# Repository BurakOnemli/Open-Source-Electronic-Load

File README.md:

# Open-Source-Electronic-Load

Welcome to the **Open-Source Electronic Load** project!

This repository provides the design, source code, and documentation for a customizable, open-source electronic load. The project is developed in C and aims to offer a platform for electronics enthusiasts, students, and engineers who need a programmable load for testing power supplies, batteries, or other electronic circuits.

## Features

- Fully open-source hardware and firmware
- Designed for flexibility and expandability
- Suitable for testing DC power supplies and batteries
- Customizable load profiles (constant current, constant power, etc.)

## Repository Structure

- **Firmware**: Source code for the microcontroller that controls the electronic load
- **Hardware**: Schematics, PCB layouts, and hardware documentation
- **Documentation**: User guides and developer notes

## Getting Started

1. **Clone the repository:**  
   `git clone https://github.com/BurakOnemli/Open-Source-Electronic-Load.git`
2. **Review the hardware documents** to understand the design and required components.
3. **Build the hardware** according to the provided schematics and BOM.
4. **Flash the firmware** onto the chosen microcontroller.

## Dependencies

- STM32CubeIDE toolchain for programming the microcontroller
- KiCad for PCB design 
- Standard electronics lab tools for assembly

## Contributing

Contributions are welcome! You can contribute by:
- Submitting pull requests for code improvements or bug fixes
- Sharing hardware modifications
- Improving the documentation

Before contributing, please review any guidelines in the repository.

## License

This project is open-source. Please see the repository for license details.

## More Information

Check the [GitHub repository](https://github.com/BurakOnemli/Open-Source-Electronic-Load) for the latest updates, issues, and discussions.

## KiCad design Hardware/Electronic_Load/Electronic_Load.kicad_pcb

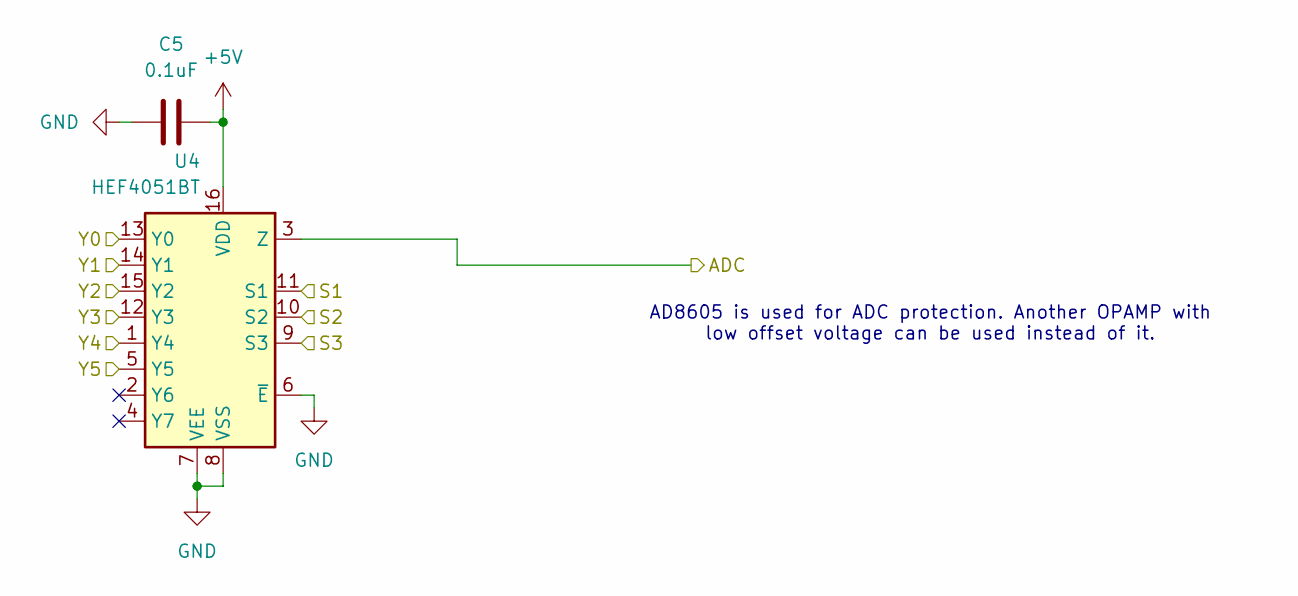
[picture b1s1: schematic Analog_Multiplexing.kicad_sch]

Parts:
C5: 0.1uF; C_0603_1608Metric
U4: HEF4051BT; SOIC-16_3.9x9.9mm_P1.27mm

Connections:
+5V: C5.2, U4.16 (VDD); also elsewhere on the board
/Analog_Multiplexing/ADC: U4.3 (Z); also elsewhere on the board
/Analog_Multiplexing/S1: U4.11 (S1); also elsewhere on the board
/Analog_Multiplexing/S2: U4.10 (S2); also elsewhere on the board
/Analog_Multiplexing/S3: U4.9 (S3); also elsewhere on the board
/Analog_Multiplexing/Y0: U4.13 (Y0); also elsewhere on the board
/Analog_Multiplexing/Y1: U4.14 (Y1); also elsewhere on the board
/Analog_Multiplexing/Y2: U4.15 (Y2); also elsewhere on the board
/Analog_Multiplexing/Y3: U4.12 (Y3); also elsewhere on the board
/Analog_Multiplexing/Y4: U4.1 (Y4); also elsewhere on the board
/Analog_Multiplexing/Y5: U4.5 (Y5); also elsewhere on the board
GND: C5.1, U4.6 (~E), U4.7 (VEE), U4.8 (VSS); also elsewhere on the board

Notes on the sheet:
AD8605 is used for ADC protection. Another OPAMP with low offset voltage can be used instead of it.

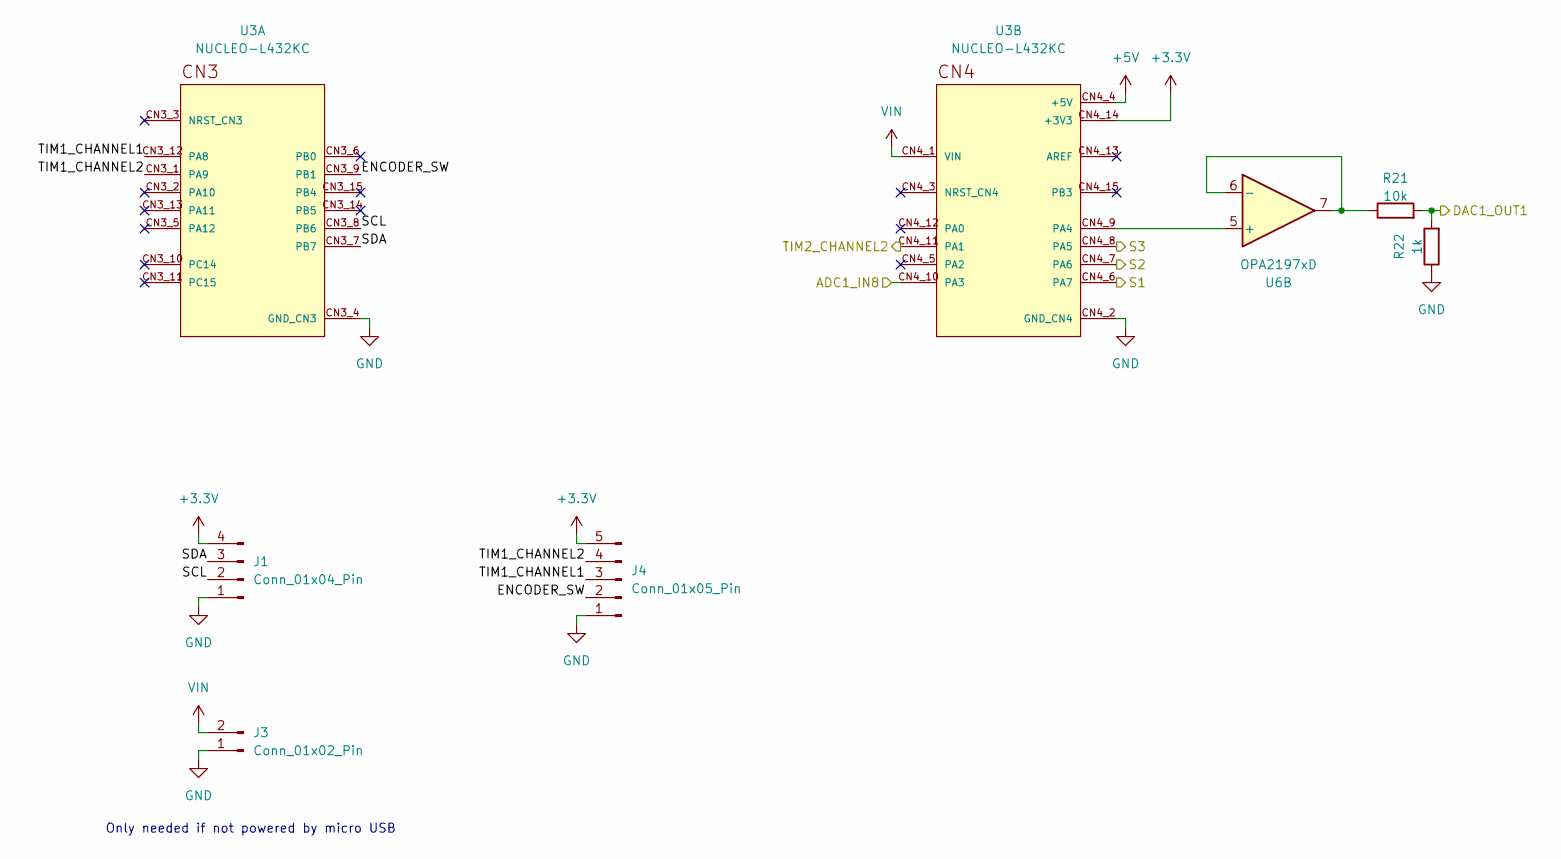
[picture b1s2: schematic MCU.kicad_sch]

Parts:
J1: Conn_01x04_Pin; PinHeader_1x04_P2.54mm_Vertical
J3: Conn_01x02_Pin; PinHeader_1x02_P2.54mm_Vertical
J4: Conn_01x05_Pin; PinHeader_1x05_P2.54mm_Vertical
R21: 10k; R_0603_1608Metric
R22: 1k; R_0603_1608Metric
U3: NUCLEO-L432KC; MODULE_NUCLEO-L432KC; PARTREV N/A
U6: OPA2197xD; SOIC-8_3.9x4.9mm_P1.27mm

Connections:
+3.3V: J1.4, J4.5, U3.CN4_14 (+3V3); also elsewhere on the board
+5V: U3.CN4_4 (+5V); also elsewhere on the board
/Analog_Multiplexing/ADC: U3.CN4_10 (PA3); also elsewhere on the board
/Analog_Multiplexing/S1: U3.CN4_6 (PA7); also elsewhere on the board
/Analog_Multiplexing/S2: U3.CN4_7 (PA6); also elsewhere on the board
/Analog_Multiplexing/S3: U3.CN4_8 (PA5); also elsewhere on the board
/Fan Controller/IN1: U3.CN4_11 (PA1); also elsewhere on the board
/Load Stage/DAC_BUFFERED: R21.2, R22.2; also elsewhere on the board
/MCU/ENCODER_SW: J4.2, U3.CN3_9 (PB1)
/MCU/SCL: J1.2, U3.CN3_8 (PB6)
/MCU/SDA: J1.3, U3.CN3_7 (PB7)
/MCU/TIM1_CHANNEL1: J4.3, U3.CN3_12 (PA8)
/MCU/TIM1_CHANNEL2: J4.4, U3.CN3_1 (PA9)
GND: J1.1, J3.1, J4.1, R22.1, U3.CN3_4 (GND_CN3), U3.CN4_2 (GND_CN4); also elsewhere on the board
unnamed: U3.CN4_9 (PA4), U6.5 (+)
unnamed: R21.1, U6.6 (-), U6.7
VIN: J3.2, U3.CN4_1 (VIN); also elsewhere on the board

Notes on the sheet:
Only needed if not powered by micro USB

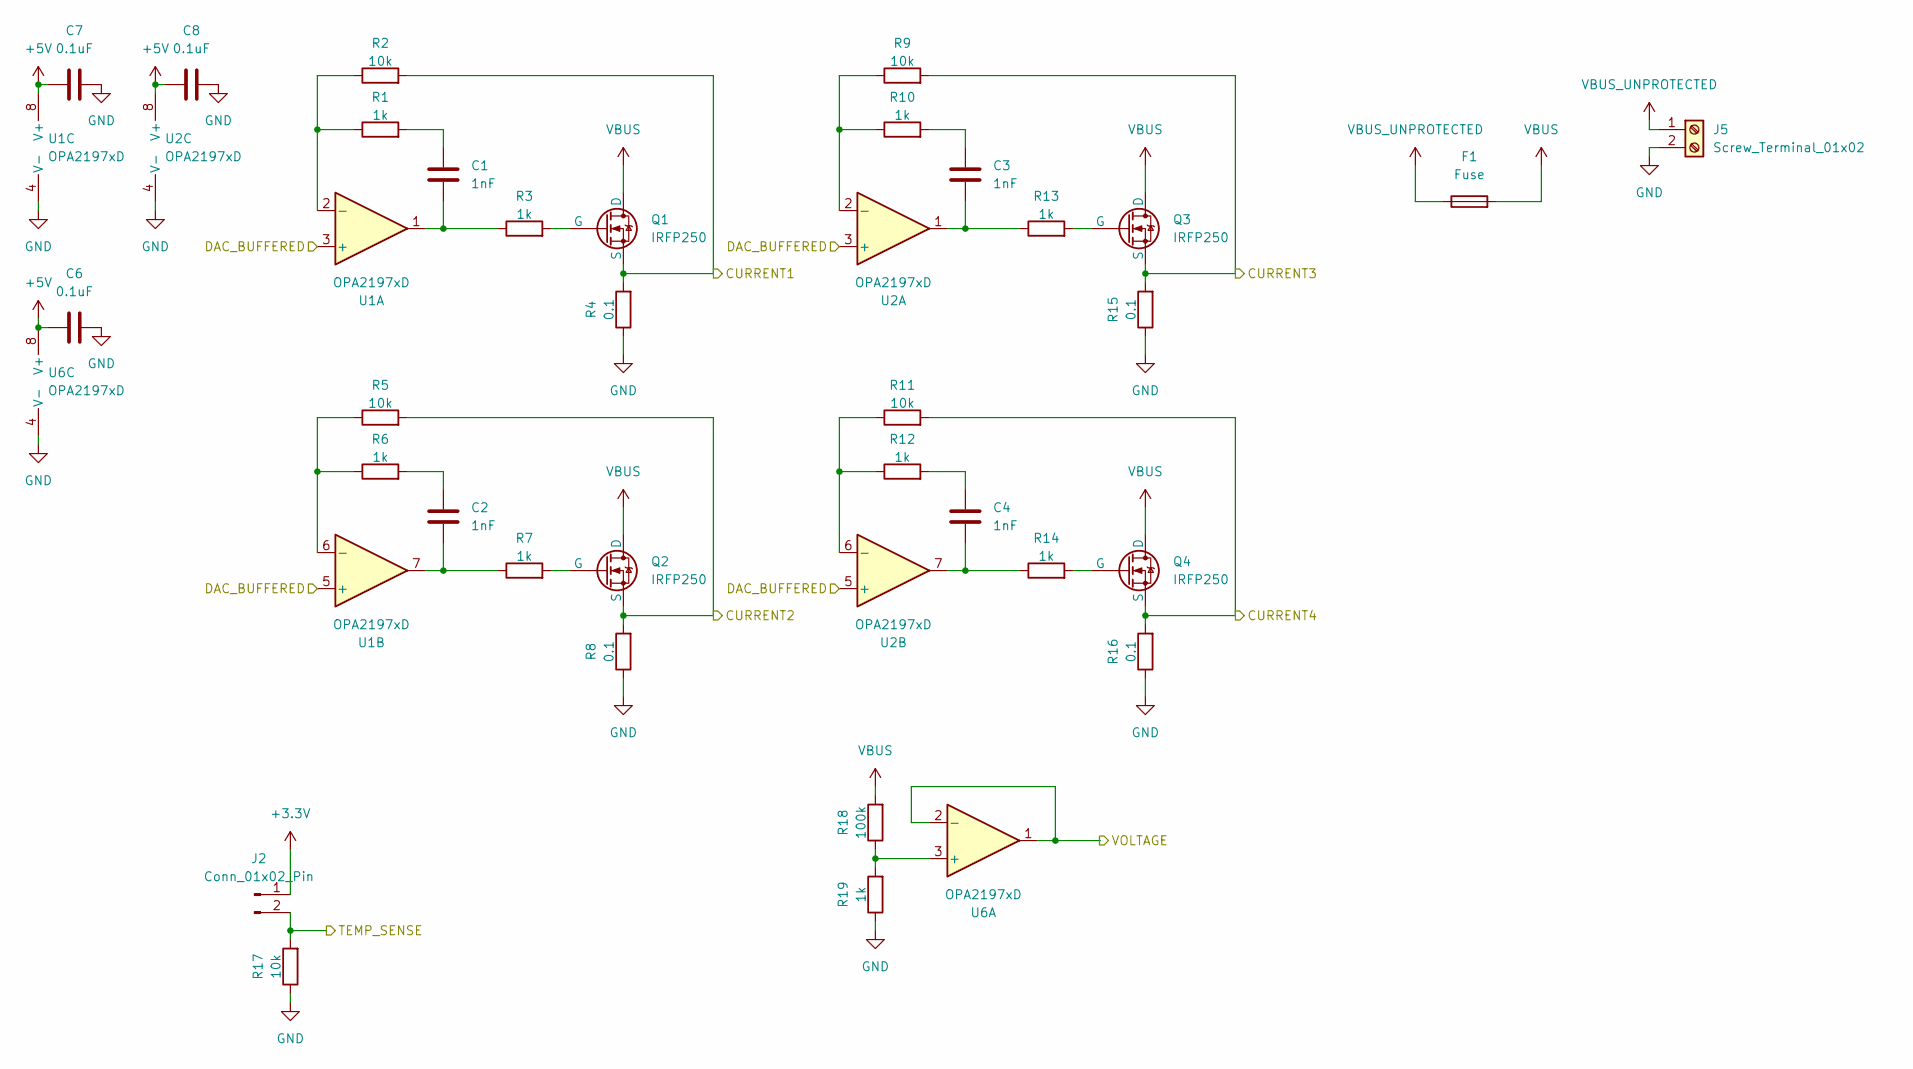
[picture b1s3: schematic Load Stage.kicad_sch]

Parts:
C1, C2, C3, C4: 1nF; C_0603_1608Metric
C6, C7, C8: 0.1uF; C_0603_1608Metric
F1: Fuse; Fuseholder_Cylinder-5x20mm_Schurter_0031_8201_Horizontal_Op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
J2: Conn_01x02_Pin; PinHeader_1x02_P2.54mm_Vertical
J5: Screw_Terminal_01x02; TerminalBlock_Wuerth_691311400102_P7.62mm
Q1, Q2, Q3, Q4: IRFP250; TO-247-3_Vertical
R1, R3, R6, R7, R10, R12, R13, R14, R19: 1k; R_0603_1608Metric
R2, R5, R9, R11, R17: 10k; R_0603_1608Metric
R4, R8, R15, R16: 0.1; R_2512_6332Metric_Pad1.40x3.35mm_HandSolder
R18: 100k; R_0603_1608Metric
U1, U2, U6: OPA2197xD; SOIC-8_3.9x4.9mm_P1.27mm

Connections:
+3.3V: J2.1; also elsewhere on the board
+5V: C6.1, C7.1, C8.1, U1.8 (V+), U2.8 (V+), U6.8 (V+); also elsewhere on the board
/Analog_Multiplexing/Y0: Q2.3 (S), R5.2, R8.2; also elsewhere on the board
/Analog_Multiplexing/Y1: Q3.3 (S), R9.2, R15.2; also elsewhere on the board
/Analog_Multiplexing/Y2: Q4.3 (S), R11.2, R16.2; also elsewhere on the board
/Analog_Multiplexing/Y3: Q1.3 (S), R2.2, R4.2; also elsewhere on the board
/Analog_Multiplexing/Y4: J2.2, R17.2; also elsewhere on the board
/Analog_Multiplexing/Y5: U6.1, U6.2 (-); also elsewhere on the board
/Load Stage/DAC_BUFFERED: U1.3 (+), U1.5 (+), U2.3 (+), U2.5 (+); also elsewhere on the board
GND: C6.2, C7.2, C8.2, J5.2, R4.1, R8.1, R15.1, R16.1, R17.1, R19.1, U1.4 (V-), U2.4 (V-), U6.4 (V-); also elsewhere on the board
unnamed: C1.1, R1.2
unnamed: C1.2, R3.1, U1.1
unnamed: C2.1, R6.2
unnamed: C2.2, R7.1, U1.7
unnamed: C3.1, R10.2
unnamed: C3.2, R13.1, U2.1
unnamed: C4.1, R12.2
unnamed: C4.2, R14.1, U2.7
unnamed: Q1.1 (G), R3.2
unnamed: Q2.1 (G), R7.2
unnamed: Q3.1 (G), R13.2
unnamed: Q4.1 (G), R14.2
unnamed: R1.1, R2.1, U1.2 (-)
unnamed: R5.1, R6.1, U1.6 (-)
unnamed: R9.1, R10.1, U2.2 (-)
unnamed: R11.1, R12.1, U2.6 (-)
unnamed: R18.1, R19.2, U6.3 (+)
VBUS: F1.2, Q1.2 (D), Q2.2 (D), Q3.2 (D), Q4.2 (D), R18.2
VBUS_UNPROTECTED: F1.1, J5.1

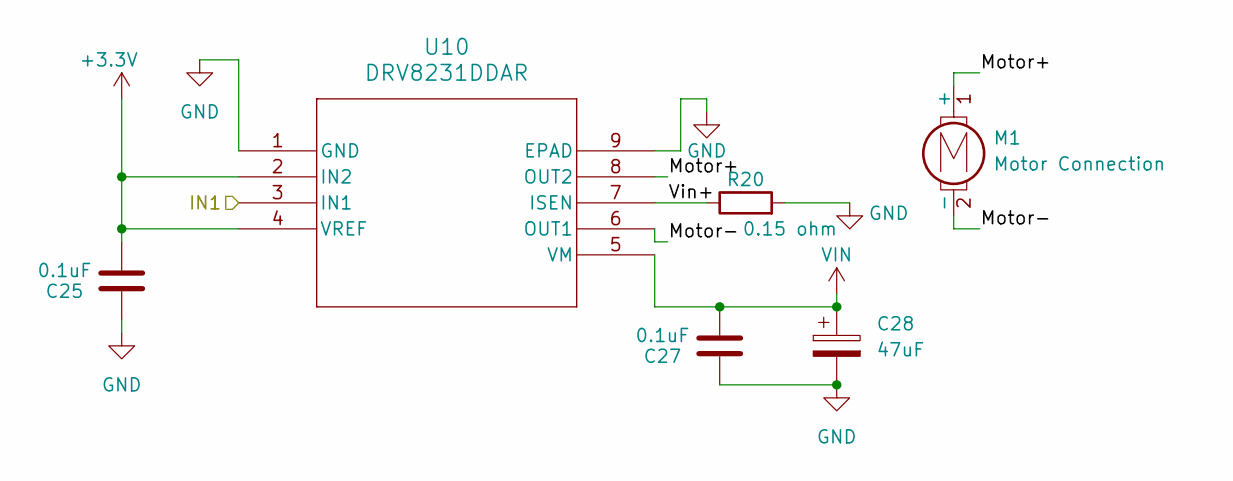
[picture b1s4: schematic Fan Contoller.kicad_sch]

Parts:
C25, C27: 0.1uF; C_0603_1608Metric
C28: 47uF; CP_EIA-6032-15_Kemet-U
M1: Motor Connection; PinHeader_1x02_P2.54mm_Vertical
R20: 0.15 ohm; R_2010_5025Metric
U10: DRV8231DDAR

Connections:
+3.3V: C25.2, U10.2 (IN2), U10.4 (VREF); also elsewhere on the board
/Fan Controller/IN1: U10.3 (IN1); also elsewhere on the board
/Fan Controller/Motor+: M1.1 (+), U10.8 (OUT2)
/Fan Controller/Motor-: M1.2 (-), U10.6 (OUT1)
/Fan Controller/Vin+: R20.1, U10.7 (ISEN)
GND: C25.1, C27.1, C28.2, R20.2, U10.1 (GND), U10.9 (EPAD); also elsewhere on the board
VIN: C27.2, C28.1, U10.5 (VM); also elsewhere on the board

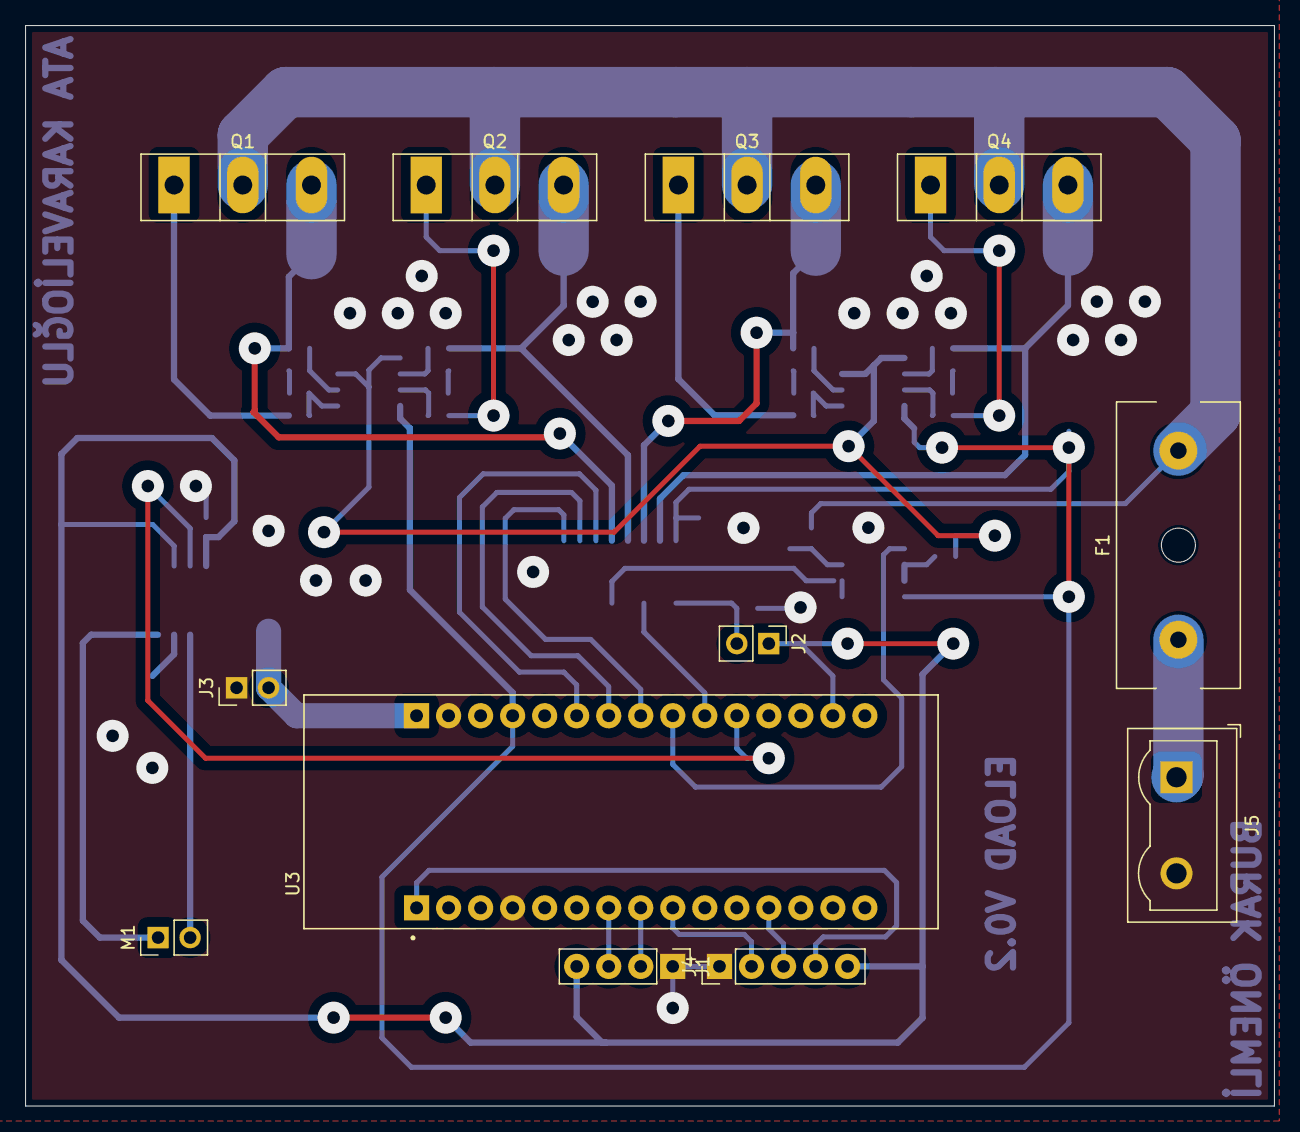
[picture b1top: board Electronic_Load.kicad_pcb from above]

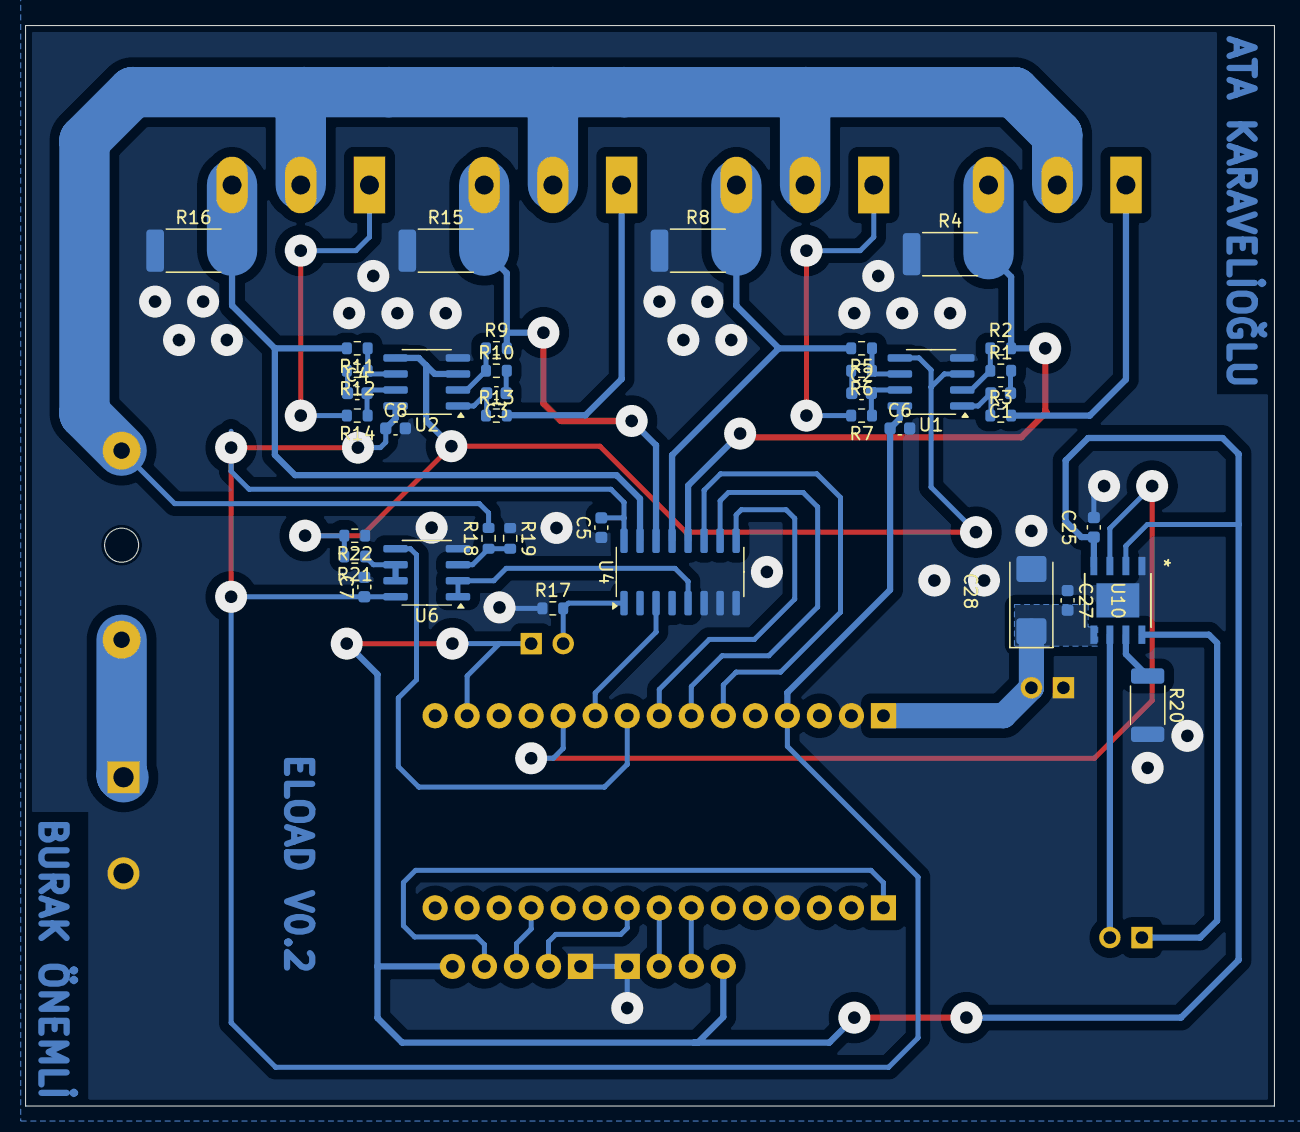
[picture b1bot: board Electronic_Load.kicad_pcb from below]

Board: 2 copper layers, 99.1 x 85.7 mm, 50 parts (38 on the bottom side), 45 nets.

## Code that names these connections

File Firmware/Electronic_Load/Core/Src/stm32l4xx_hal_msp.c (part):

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
    __HAL_RCC_GPIOA_CLK_ENABLE();
    /**ADC1 GPIO Configuration
    PA3     ------> ADC1_IN8
    */
    GPIO_InitStruct.Pin = GPIO_PIN_3;
    GPIO_InitStruct.Mode = GPIO_MODE_ANALOG_ADC_CONTROL;
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    __HAL_RCC_ADC_CLK_DISABLE();

    /**ADC1 GPIO Configuration
    PA3     ------> ADC1_IN8
    */
    HAL_GPIO_DeInit(GPIOA, GPIO_PIN_3);

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
    __HAL_RCC_GPIOA_CLK_ENABLE();
    /**DAC1 GPIO Configuration
    PA4     ------> DAC1_OUT1
    */
    GPIO_InitStruct.Pin = GPIO_PIN_4;
    GPIO_InitStruct.Mode = GPIO_MODE_ANALOG;
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    __HAL_RCC_DAC1_CLK_DISABLE();

    /**DAC1 GPIO Configuration
    PA4     ------> DAC1_OUT1
    */
    HAL_GPIO_DeInit(GPIOA, GPIO_PIN_4);

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
    __HAL_RCC_GPIOB_CLK_ENABLE();
    /**I2C1 GPIO Configuration
    PB6     ------> I2C1_SCL
    PB7     ------> I2C1_SDA
    */
    GPIO_InitStruct.Pin = GPIO_PIN_6|GPIO_PIN_7;
    GPIO_InitStruct.Mode = GPIO_MODE_AF_OD;
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    __HAL_RCC_I2C1_CLK_DISABLE();

    /**I2C1 GPIO Configuration
    PB6     ------> I2C1_SCL
    PB7     ------> I2C1_SDA
    */
    HAL_GPIO_DeInit(GPIOB, GPIO_PIN_6);

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
    __HAL_RCC_GPIOA_CLK_ENABLE();
    /**TIM1 GPIO Configuration
    PA8     ------> TIM1_CH1
    PA9     ------> TIM1_CH2
    */
    GPIO_InitStruct.Pin = GPIO_PIN_8|GPIO_PIN_9;
    GPIO_InitStruct.Mode = GPIO_MODE_AF_PP;
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    __HAL_RCC_TIM1_CLK_DISABLE();

    /**TIM1 GPIO Configuration
    PA8     ------> TIM1_CH1
    PA9     ------> TIM1_CH2
    */
    HAL_GPIO_DeInit(GPIOA, GPIO_PIN_8|GPIO_PIN_9);

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
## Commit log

2025-09-10 Electronic Load V0.2
2025-09-10 Enhance README with project details and instructions
2025-09-10 Update project description in README.md
    Removed the word 'flexible' from the project description.
2025-09-10 Revise dependencies and license information in README
    Updated dependencies section and clarified license statement.
2025-09-10 Add image to README for project visualization
    Added an image to the README for better visual appeal.

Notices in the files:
Firmware/Electronic_Load/Core/Src/stm32l4xx_hal_msp.c:
Copyright (c) 2025 STMicroelectronics.
All rights reserved.
This software is licensed under terms that can be found in the LICENSE file
